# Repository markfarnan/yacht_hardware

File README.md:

# yacht_hardware
Various sensor circuits and boards for Yachts

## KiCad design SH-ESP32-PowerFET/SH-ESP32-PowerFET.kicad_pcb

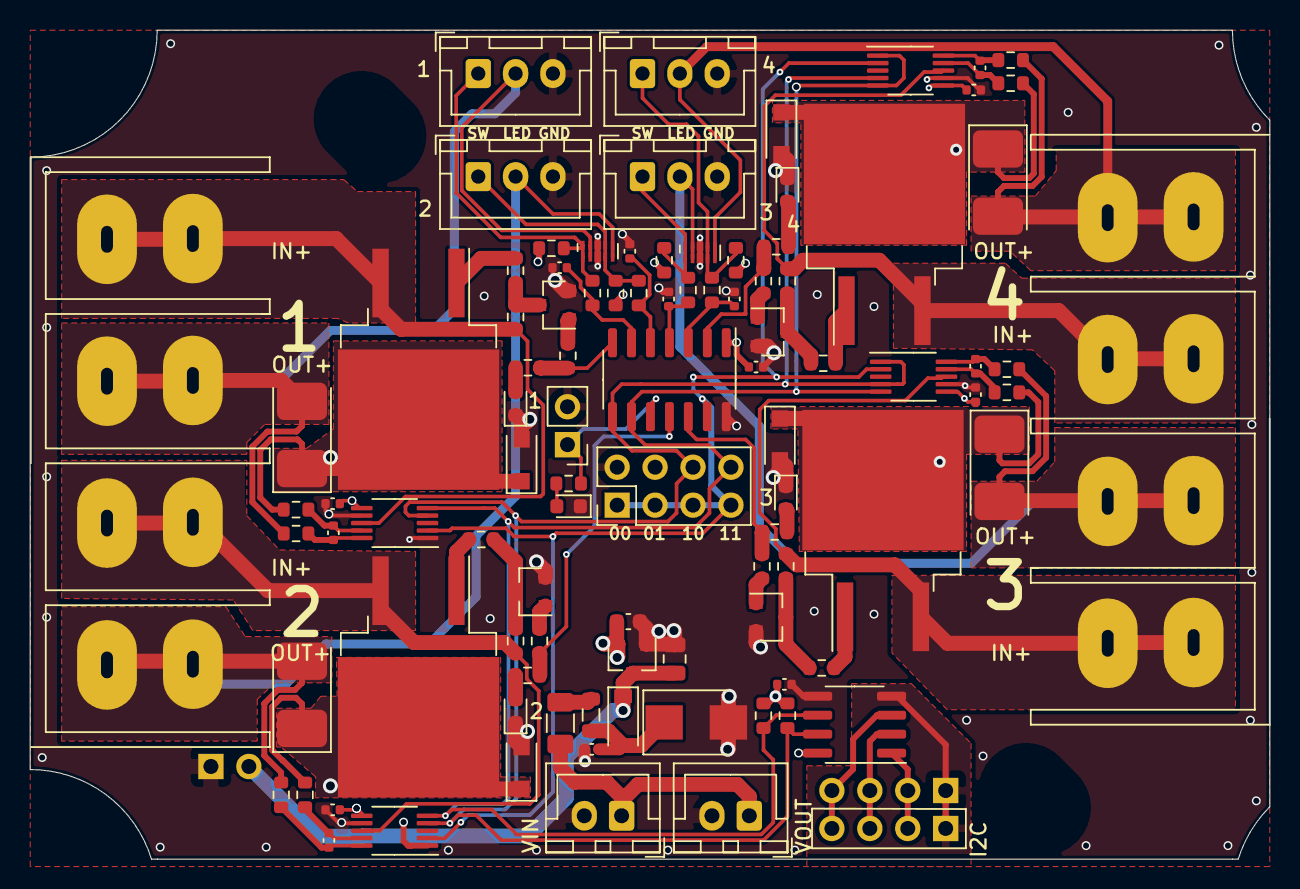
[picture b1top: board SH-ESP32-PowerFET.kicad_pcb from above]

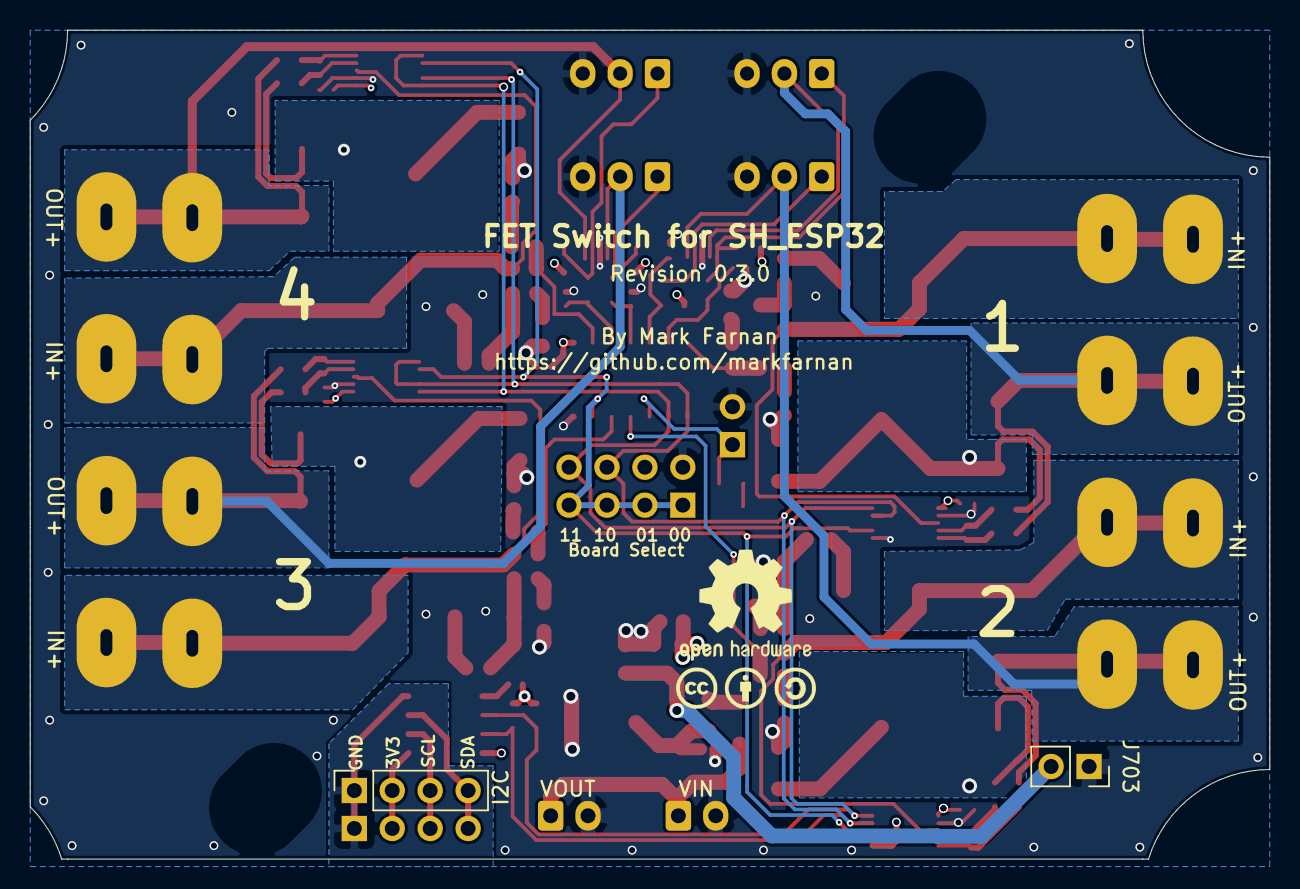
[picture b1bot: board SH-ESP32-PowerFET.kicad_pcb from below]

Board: 4 copper layers, 83.0 x 55.5 mm, 101 parts (2 on the bottom side), 63 nets.

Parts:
C101, C102, C103, C104: 1nf; C_0402_1005Metric
C201, C202, C203, C204, C205, C206, C301, C401, C501, C601: 100nF; C_0402_1005Metric
C701: 2.2uF/50V; C_0805_2012Metric
C702: 10nF/50V; C_0402_1005Metric
C703: 2.2uF/16V; C_0603_1608Metric
D101: RED LED; LED_0603_1608Metric
D301, D401, D501, D601: BLUE LED; LED_0603_1608Metric
D302, D402, D502, D602: SM4007PL; D_SOD-123F
D701: SMBJ33CA; D_SMB
D703: B5819W; D_SOD-123
F701: FSMD012-1206-R; Fuse_1206_3216Metric
FB701: GZ2012D601TF; L_0805_2012Metric
H201, H202: MountingHole; MountingSlot_3.2mm_M3_Unplated
J101: DBT50G-9.5-4P; Connector_9.5mm_ScrewTerminal_4
J102: DBT50G-9.5-2P; Connector_9.5mm_ScrewTerminal_4
J103: AddressSelect; PinHeader_2x04_P2.54mm_Vertical_ReducedCY_Jumper
J105: UPDI; PinHeader_1x02_P2.54mm_Vertical
J106: I2C; PinSocket_1x04_P2.54mm_Vertical
J107, J108, J110, J111: Switch; JST_XH_B3B-XH-A_1x03_P2.50mm_Vertical
J109: I2C; PinHeader_1x04_P2.54mm_Vertical-ShrunkCY
J701: VIN; JST_XH_B2B-XH-A_1x02_P2.50mm_Vertical
J702: VOUT; JST_XH_B2B-XH-A_1x02_P2.50mm_Vertical
J703: VOUT; PinSocket_1x02_P2.54mm_Vertical
Q301, Q401, Q501, Q601: IRLML0030; SOT-23
Q302, Q402, Q502, Q602: IRF5210STRLPBF; TO-263-2
R101, R106, R107, R108, R109, R301, R401, R501, R601: 2k; R_0603_1608Metric
R102, R103, R104, R105, R110, R111, R303, R403, R503, R603: 10k; R_0603_1608Metric
R302, R402, R502, R602: 220R; R_0603_1608Metric
R304, R404, R504, R604: 1k; R_0603_1608Metric
R305, R405, R505, R605: 0.002ohm/3W; D_2512_Shunt
R306, R307, R406, R407, R506, R507, R606, R607: 10R; R_0603_1608Metric
U101: ATtiny1614-SSNR; SOIC-14_3.9x8.7mm_P1.27mm
U102: ISO1540; SOIC-8_3.9x4.9mm_P1.27mm
U103, U701: RCLAMP0524P-N; Diodes_UDFN-10_1.0x2.5mm_P0.5mm
U301, U401, U501, U601: INA226AIDGSR; VSSOP-10_3x3mm_P0.5mm
U702: H7533-H#; SOT-23

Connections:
+3V3: C201.2, C202.2, C203.2, C204.2, C205.2, C206.2, C703.1, J103.4, R102.1, R103.1, R104.1, R105.1, R110.1, R111.1, U101.1, U102.8, U301.6, U401.1, U401.6, U501.6, U601.6, U702.2
/ASEL: J103.1, J103.3, J103.5, J103.7, U101.13, U301.2, U401.2, U501.2, U601.2
/DRVOUT_01: J101.2, J107.2, R305.3, R305.4, R307.2, U701.2, U701.9
/DRVOUT_02: J101.4, J108.2, R405.3, R405.4, R407.2, U701.5, U701.6
/DRVOUT_03: J102.2, J110.2, R505.3, R505.4, R507.2, U103.2, U103.9
/DRVOUT_04: J102.4, J111.2, R605.3, R605.4, R607.2, U103.5, U103.6
/DRVPWR_01: J101.1, Q302.3, R303.1, U301.8
/DRVPWR_02: J101.3, Q402.3, R403.1, U401.8
/DRVPWR_03: J102.1, Q502.3, R503.1, U501.8
/DRVPWR_04: J102.3, Q602.3, R603.1, U601.8
/FET01/VOUT: D302.1, Q302.2, R305.1, R305.2, R306.1
/FET02/VOUT: D402.1, Q402.2, R405.1, R405.2, R406.1
/FET03/VOUT: D502.1, Q502.2, R505.1, R505.2, R506.1
/FET04/VOUT: D602.1, Q602.2, R605.1, R605.2, R606.1
/FETDRIVE_01: R301.1, R302.2, U101.7
/FETDRIVE_02: R401.1, R402.2, U101.11
/FETDRIVE_03: R501.1, R502.2, U101.12
/FETDRIVE_04: R601.1, R602.2, U101.2
/Power-Input/Vin: F701.2, J701.1, J702.1
/Power-Input/Vin_fused: C702.1, D701.1, D703.2, FB701.1
/Power-Input/Vin_protected: C701.1, D703.1, J703.2, U702.3
/SCL: J103.8, R111.2, U101.9, U102.6, U301.5, U401.5, U501.5, U601.1, U601.5
/SCL_CONN: J106.4, J109.4, U102.3
/SDA: J103.6, R110.2, U101.8, U102.7, U301.4, U401.4, U501.1, U501.4, U601.4
/SDA_CONN: J106.3, J109.3, U102.2
/SWIN_1: J107.1, R102.2, R106.2, U701.1, U701.10
/SWIN_2: J108.1, R103.2, R107.2, U701.4, U701.7
/SWIN_3: J110.1, R104.2, R108.2, U103.1, U103.10
/SWIN_4: J111.1, R105.2, R109.2, U103.4, U103.7
/SWITCH_01: C101.1, R106.1, U101.6
/SWITCH_02: C102.1, R107.1, U101.5
/SWITCH_03: C103.1, R108.1, U101.4
/SWITCH_04: C104.1, R109.1, U101.3
/UPDI_LED: J105.1, R101.1, U101.10
/VCC_CONN_3V3: J106.2, J109.2, U102.1
GND: C101.2, C102.2, C103.2, C104.2, C201.1, C202.1, C203.1, C204.1, C205.1, C206.1, C701.2, C702.2, C703.2, D101.1, D301.1, D302.2, D401.1, D402.2, D501.1, D502.2, D601.1, D602.2, D701.2, J103.2, J105.2, J107.3, J108.3, J110.3, J111.3, J701.2, J702.2, J703.1, Q301.2, Q401.2, Q501.2, Q601.2, U101.14, U102.5, U103.3, U103.8, U301.1, U301.7, U401.7, U501.7, U601.7, U701.3, U701.8, U702.1
GNDA: J106.1, J109.1, U102.4
unnamed: C301.1, R306.2, U301.9
unnamed: C301.2, R307.1, U301.10
unnamed: C401.1, R406.2, U401.9
unnamed: C401.2, R407.1, U401.10
unnamed: C501.1, R506.2, U501.9
unnamed: C501.2, R507.1, U501.10
unnamed: C601.1, R606.2, U601.9
unnamed: C601.2, R607.1, U601.10
unnamed: D101.2, R101.2
unnamed: D301.2, R301.2
unnamed: D401.2, R401.2
unnamed: D501.2, R501.2
unnamed: D601.2, R601.2
unnamed: F701.1, FB701.2
unnamed: Q301.1, R302.1
unnamed: Q301.3, R303.2, R304.2
unnamed: Q302.1, R304.1
unnamed: Q401.1, R402.1
unnamed: Q401.3, R403.2, R404.2
unnamed: Q402.1, R404.1
unnamed: Q501.1, R502.1
unnamed: Q501.3, R503.2, R504.2
unnamed: Q502.1, R504.1
unnamed: Q601.1, R602.1
unnamed: Q601.3, R603.2, R604.2
unnamed: Q602.1, R604.1

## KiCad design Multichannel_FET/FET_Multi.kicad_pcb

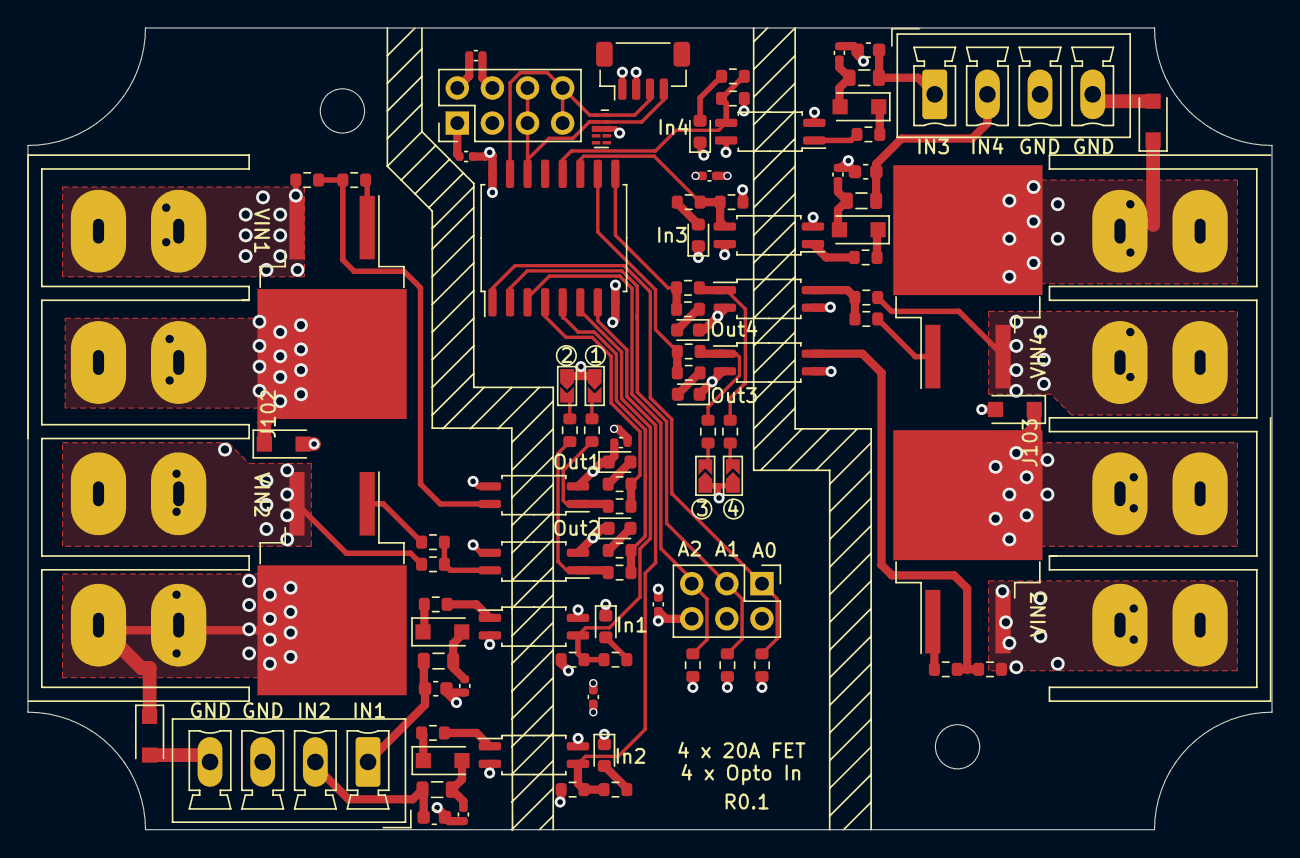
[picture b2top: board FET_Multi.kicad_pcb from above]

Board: 4 copper layers, 90.0 x 58.0 mm, 96 parts (0 on the bottom side), 65 nets.

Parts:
C301, C303, C305, C307: 33pF; C_0402_1005Metric
C302, C304, C306, C308: 33pF/50V; C_0603_1608Metric
C1001, C1002, C1003, C1004, C1005, C1006: 100nF; C_0402_1005Metric
D101, D103, D105, D107, D301, D303, D305, D307: GREEN LED; LED_0603_1608Metric
D102, D104, D106, D108, D302, D304, D306, D308: SM4007PL; D_SOD-123F
FB301, FB302, FB303, FB304: GZ2012D101TF; L_0805_2012Metric
H1001, H1002: MountingHole; MountingHole_3.2mm_M3_Unplated
J101: I2C; PinHeader_2x04_P2.54mm_Vertical
J102, J103: DBT50G-9.5-4P; Connector_9.5mm_ScrewTerminal_4-Reversable
J104: Conn_01x04; JST_SH_BM04B-SRSS-TB_1x04-1MP_P1.00mm_Vertical
J106: ADDR; PinHeader_2x03_P2.54mm_Vertical
J107, J108, J109, J110: PU_ON; SolderJumper-2_P1.3mm_Open_TrianglePad_Narrow
J302, J303: MC 4; PhoenixContact_MCV_1,5_4-G-3.81_1x04_P3.81mm_Vertical
Q101, Q102, Q103, Q104: IRF5210STRLPBF; TO-263-2
R101, R105, R109, R113, R305, R307, R311, R312: 2k; R_0603_1608Metric
R102, R106, R110, R114: 220R; R_0603_1608Metric
R103, R107, R111, R115, R117, R118, R119: 10k; R_0603_1608Metric
R104, R108, R112, R116, R120, R121, R122, R123: 1k; R_0603_1608Metric
R301, R302, R303, R304, R306, R308, R309, R310: 2.2k; R_0603_1608Metric
U101, U102, U103, U104, U301, U302, U303, U304: EL3H7(C)(TA)-G; SOP-4_4.4x2.6mm_P1.27mm
U105: PCF8574T/3,518; SOIC-16W_7.5x10.3mm_P1.27mm
U106: RCLAMP0524P-N; Diodes_UDFN-10_1.0x2.5mm_P0.5mm

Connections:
+3V3: C1001.2, C1002.2, C1003.2, C1004.2, C1005.2, C1006.2, J101.3, J101.4, J104.2, J106.2, J106.4, J106.6, J107.1, J108.1, J109.1, J110.1, U105.16, U301.4, U302.4, U303.4, U304.4
/A0: J106.1, R119.1, U105.1
/A1: J106.3, R118.1, U105.2
/A2: J106.5, R117.1, U105.3
/GPIO0: R101.1, R102.2, U105.4
/GPIO1: R105.1, R106.2, U105.5
/GPIO4: R113.1, R114.2, U105.9
/GPIO5: R109.1, R110.2, U105.10
/Opto Input/ISO_IN_1: C302.1, FB301.1, J302.1
/Opto Input/ISO_IN_2: C304.1, FB302.1, J302.2
/Opto Input/ISO_IN_3: C306.1, FB303.1, J303.1
/Opto Input/ISO_IN_4: C308.1, FB304.1, J303.2
/SCL: J101.5, J101.6, J104.4, U105.14, U106.2, U106.9
/SDA: J101.7, J101.8, J104.3, U105.15, U106.1, U106.10
/VIN1: J102.1, Q101.3, R103.1
/VIN2: J102.3, Q102.3, R107.1
/VIN3: J103.1, Q103.3, R111.1
/VIN4: J103.3, Q104.3, R115.1
/VOUT1: D102.1, J102.2, Q101.2
/VOUT2: D104.1, J102.4, Q102.2
/VOUT3: D106.1, J103.2, Q103.2
/VOUT4: D108.1, J103.4, Q104.2
GND: C1001.1, C1002.1, C1003.1, C1004.1, C1005.1, C1006.1, D101.1, D103.1, D105.1, D107.1, D301.1, D303.1, D305.1, D307.1, J101.1, J101.2, J104.1, R117.2, R118.2, R119.2, R301.1, R303.1, R309.1, R310.1, U101.2, U102.2, U103.2, U104.2, U105.8, U106.3, U106.8
GND1: C301.2, C302.2, C303.2, C304.2, D102.2, D104.2, J302.3, J302.4, U101.3, U102.3, U301.2, U302.2
GND2: C305.2, C306.2, C307.2, C308.2, D106.2, D108.2, J303.3, J303.4, U103.3, U104.3, U303.2, U304.2
GPIO2: R301.2, R305.1, U105.6, U301.3
GPIO3: R303.2, R307.1, U105.7, U302.3
GPIO6: R309.2, R311.1, U105.11, U303.3
GPIO7: R310.2, R312.1, U105.12, U304.3
unnamed: C301.1, D302.2, FB301.2
unnamed: C303.1, D304.2, FB302.2
unnamed: C305.1, D306.2, FB303.2
unnamed: C307.1, D308.2, FB304.2
unnamed: D101.2, R101.2
unnamed: D103.2, R105.2
unnamed: D105.2, R109.2
unnamed: D107.2, R113.2
unnamed: D301.2, R305.2
unnamed: D302.1, R302.1
unnamed: D303.2, R307.2
unnamed: D304.1, R304.1
unnamed: D305.2, R311.2
unnamed: D306.1, R306.1
unnamed: D307.2, R312.2
unnamed: D308.1, R308.1
unnamed: J107.2, R120.1
unnamed: J108.2, R121.1
unnamed: J109.2, R122.1
unnamed: J110.2, R123.1
unnamed: Q101.1, R104.1
unnamed: Q102.1, R108.1
unnamed: Q103.1, R112.1
unnamed: Q104.1, R116.1
unnamed: R102.1, R120.2, U101.1
unnamed: R103.2, R104.2, U101.4
unnamed: R106.1, R121.2, U102.1
unnamed: R107.2, R108.2, U102.4
unnamed: R110.1, R123.2, U103.1
unnamed: R111.2, R112.2, U103.4
unnamed: R114.1, R122.2, U104.1
unnamed: R115.2, R116.2, U104.4
unnamed: R302.2, U301.1
unnamed: R304.2, U302.1
unnamed: R306.2, U304.1
unnamed: R308.2, U303.1

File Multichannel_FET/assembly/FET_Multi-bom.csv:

Comment,Designator,Footprint,LCSC
"100nF","C1001,C1002,C1003,C1004,C1005,C1006","Capacitor_SMD:C_0402_1005Metric","C1525"
"33pF","C301,C303,C305,C307","Capacitor_SMD:C_0402_1005Metric","C1562"
"33pF/50V","C302,C304,C306,C308","Capacitor_SMD:C_0603_1608Metric","C1663"
"GREEN LED","D101,D103,D105,D107,D301,D303,D305,D307","LED_SMD:LED_0603_1608Metric","C72043"
"SM4007PL","D102,D104,D106,D108,D302,D304,D306,D308","Diode_SMD:D_SOD-123F","C64898"
"GZ2012D101TF","FB301,FB302,FB303,FB304","Inductor_SMD:L_0805_2012Metric","C1015"
"MountingHole","H1001,H1002","SH-ESP32:MountingHole_3.2mm_M3_Unplated",""
"I2C","J101","Connector_PinHeader_2.54mm:PinHeader_2x04_P2.54mm_Vertical",""
"DBT50G-9.5-4P","J102,J103","FET_Multi:Connector_9.5mm_ScrewTerminal_4-Reversable","C395960"
"Conn_01x04","J104","Connector_JST:JST_SH_BM04B-SRSS-TB_1x04-1MP_P1.00mm_Vertical","C145961"
"ADDR","J106","Connector_PinHeader_2.54mm:PinHeader_2x03_P2.54mm_Vertical",""
"PU_ON","J107,J108,J109,J110","FET_Multi:SolderJumper-2_P1.3mm_Open_TrianglePad_Narrow",""
"MC 4","J302,J303","Connector_Phoenix_MC:PhoenixContact_MCV_1,5_4-G-3.81_1x04_P3.81mm_Vertical","C458128"
"IRF5210STRLPBF","Q101,Q102,Q103,Q104","Package_TO_SOT_SMD:TO-263-2","C2622"
"2k","R101,R105,R109,R113,R305,R307,R311,R312","Resistor_SMD:R_0603_1608Metric","C22975"
"220R","R102,R106,R110,R114","Resistor_SMD:R_0603_1608Metric","C22962"
"10k","R103,R107,R111,R115,R117,R118,R119","Resistor_SMD:R_0603_1608Metric","C25804"
"1k","R104,R108,R112,R116,R120,R121,R122,R123","Resistor_SMD:R_0603_1608Metric","C21190"
"2.2k","R301,R302,R303,R304,R306,R308,R309,R310","Resistor_SMD:R_0603_1608Metric","C4190"
"EL3H7(C)(TA)-G","U101,U102,U103,U104,U301,U302,U303,U304","Package_SO:SOP-4_4.4x2.6mm_P1.27mm","C92243"
"PCF8574T/3,518","U105","Package_SO:SOIC-16W_7.5x10.3mm_P1.27mm","C7605"
"RCLAMP0524P-N","U106","Package_DFN_QFN:Diodes_UDFN-10_1.0x2.5mm_P0.5mm","C316044"

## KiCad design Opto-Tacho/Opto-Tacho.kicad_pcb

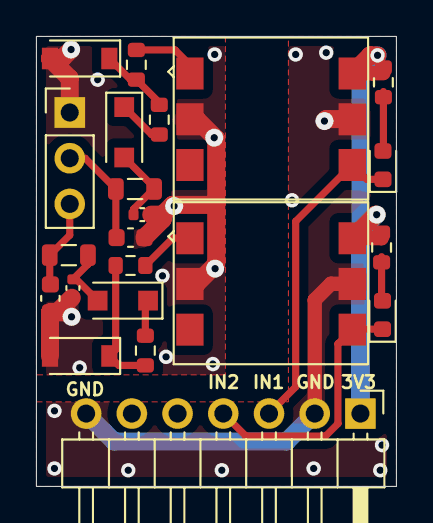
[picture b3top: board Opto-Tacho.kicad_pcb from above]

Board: 2 copper layers, 20.0 x 25.0 mm, 22 parts (0 on the bottom side), 17 nets.

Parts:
C101, C103: 33pF; C_0402_1005Metric
C102, C104: 33pF/50V; C_0603_1608Metric
D101, D104: GREEN LED; LED_0603_1608Metric
D102, D105: MM1Z4V7B; D_SOD-123
D103, D106: SM4007PL; D_SOD-123F
FB101, FB102: GZ2012D101TF; L_0805_2012Metric
J101: Interface; PinHeader_1x07_P2.54mm_Horizontal
J901: Conn_01x03; PinHeader_1x03_P2.54mm_Vertical
R101, R103, R104, R106: 1k; R_0603_1608Metric
R102, R105: 330; R_0603_1608Metric
U101, U102: H11L1SR2M; SMT-6_6.4x8.5x2.54P

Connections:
+3V3: J101.1, R101.1, R104.1, U101.6, U102.6
/GPIO_1: D101.1, J101.3, U101.4
/GPIO_2: D104.1, J101.4, U102.4
/ISO_GND: C101.2, C102.2, C103.2, C104.2, D102.2, D105.2, J901.1, U101.2, U102.2
/ISO_IN_1: C102.1, FB101.1, J901.2
/ISO_IN_2: C104.1, FB102.1, J901.3
GND: J101.2, J101.7, U101.5, U102.5
unnamed: C101.1, D103.2, FB101.2
unnamed: C103.1, D106.2, FB102.2
unnamed: D101.2, R101.2
unnamed: D102.1, R102.1, R103.2
unnamed: D103.1, R103.1
unnamed: D104.2, R104.2
unnamed: D105.1, R105.1, R106.2
unnamed: D106.1, R106.1
unnamed: R102.2, U101.1
unnamed: R105.2, U102.1

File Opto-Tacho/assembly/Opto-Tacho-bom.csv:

Comment,Designator,Footprint,LCSC
"33pF","C101,C103","Capacitor_SMD:C_0402_1005Metric","C1562"
"33pF/50V","C102,C104","Capacitor_SMD:C_0603_1608Metric","C1663"
"GREEN LED","D101,D104","LED_SMD:LED_0603_1608Metric","C72043"
"MM1Z4V7B","D102,D105","Diode_SMD:D_SOD-123","C438304"
"SM4007PL","D103,D106","Diode_SMD:D_SOD-123F","C64898"
"GZ2012D101TF","FB101,FB102","Inductor_SMD:L_0805_2012Metric","C1015"
"Interface","J101","Connector_PinHeader_2.54mm:PinHeader_1x07_P2.54mm_Horizontal",""
"Conn_01x03","J901","Connector_PinHeader_2.54mm:PinHeader_1x03_P2.54mm_Vertical","C358686"
"330","R102,R105","Resistor_SMD:R_0603_1608Metric","C23138"
"1k","R101,R103,R104,R106","Resistor_SMD:R_0603_1608Metric","C21190"
"H11L1SR2M","U101,U102","yacht_hardware:SMT-6_6.4x8.5x2.54P","C20082"

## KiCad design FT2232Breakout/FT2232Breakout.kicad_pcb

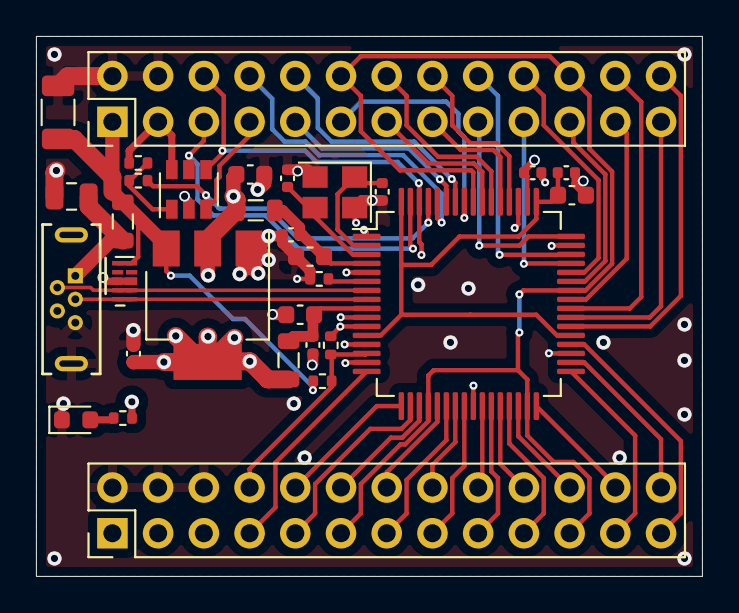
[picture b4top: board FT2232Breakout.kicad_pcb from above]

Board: 4 copper layers, 37.0 x 30.0 mm, 31 parts (0 on the bottom side), 53 nets.

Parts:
C101, C103, C109: 4.7uF/16V; C_0603_1608Metric
C102: 4.7uF; C_0603_1608Metric
C104, C107: 30pf; C_0402_1005Metric
C105, C106, C108, C110, C305: 100nF; C_0402_1005Metric
C301: 10uF/50V; C_1206_3216Metric
C503: 1uF/50V; C_0805_2012Metric
D101: RED LED; LED_0603_1608Metric
FB101, FB102, FB401: GZ2012D601TF; L_0805_2012Metric
J101: USB_B_Micro; USB_Micro-B_Wuerth_614105150721_Vertical
J102: IO2; PinHeader_2x13_P2.54mm_Vertical
J103: IO1; PinHeader_2x13_P2.54mm_Vertical
R101, R104: 10k; R_0402_1005Metric
R102: 12k; R_0402_1005Metric
R103, R106: 2k; R_0402_1005Metric
R105: 15k; R_0402_1005Metric
U101: AMS1117-3.3; SOT-223-3_TabPin2
U102: 93LC56BT-I/OT; SOT-23-6
U103: FT2232HL; LQFP-64_10x10mm_P0.5mm
U402: RCLAMP0524P-N; Diodes_UDFN-10_1.0x2.5mm_P0.5mm
Y101: X322512MSB4SI; Crystal_SMD_3225-4Pin_3.2x2.5mm

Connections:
+3V3: C101.1, C108.1, C305.1, FB101.2, FB102.2, J102.3, J103.1, J103.3, J103.5, R101.1, R106.1, U101.2, U102.6, U103.50
+5V: C301.1, FB401.1, J102.1, R105.1, U101.3, U402.5, U402.6
/AC0: J103.18, U103.26
/AC1: J103.17, U103.27
/AC2: J103.20, U103.28
/AC3: J103.19, U103.29
/AC4: J103.22, U103.30
/AC5: J103.24, U103.32
/AC6: J103.23, U103.33
/AC7: J103.26, U103.34
/AD0: J103.7, U103.16
/AD1: J103.10, U103.17
/AD2: J103.9, U103.18
/AD3: J103.12, U103.19
/AD4: J103.14, U103.21
/AD5: J103.13, U103.22
/AD6: J103.16, U103.23
/AD7: J103.15, U103.24
/BC0: J102.17, U103.48
/BC1: J102.16, U103.52
/BC2: J102.15, U103.53
/BC3: J102.14, U103.54
/BC4: J102.13, U103.55
/BC5: J102.11, U103.57
/BC6: J102.10, U103.58
/BC7: J102.9, U103.59
/BD0: J102.26, U103.38
/BD1: J102.25, U103.39
/BD2: J102.24, U103.40
/BD3: J102.23, U103.41
/BD4: J102.21, U103.43
/BD5: J102.20, U103.44
/BD6: J102.19, U103.45
/BD7: J102.18, U103.46
/CLK: J102.6, U102.4, U103.62
/CS: J102.5, U102.5, U103.63
/DATA: J102.7, R103.1, U102.3, U103.61
/PWREN#: J102.8, U103.60
/RESET#: J103.8, R104.1, R105.2, U103.14
/SUSPEND#: J103.25, U103.36
/USB_D+: J101.3, U103.8, U402.1, U402.10
/USB_D-: J101.2, U103.7, U402.2, U402.9
/VBUS: C503.1, FB401.2, J101.1
/VCORE: C102.1, C105.1, U103.12, U103.37, U103.49, U103.64
/VIO: J102.12, J102.22, J103.11, J103.21, U103.20, U103.31, U103.42, U103.56
/VPHY: C103.1, C106.1, FB102.1, U103.4
/VPLL: C109.1, C110.1, FB101.1, U103.9
GND: C101.2, C102.2, C103.2, C104.1, C105.2, C106.2, C107.1, C108.2, C109.2, C110.2, C301.2, C305.2, C503.2, D101.1, J101.5, J101.6, J102.2, J102.4, J103.2, J103.4, J103.6, R102.2, R104.2, U101.1, U102.2, U103.1, U103.5, U103.10, U103.11, U103.13, U103.15, U103.25, U103.35, U103.47, U103.51, U402.3, U402.8, Y101.2, Y101.4
unnamed: C104.2, U103.2, Y101.1
unnamed: C107.2, U103.3, Y101.3
unnamed: D101.2, R106.2
unnamed: R101.2, R103.2, U102.1
unnamed: R102.1, U103.6

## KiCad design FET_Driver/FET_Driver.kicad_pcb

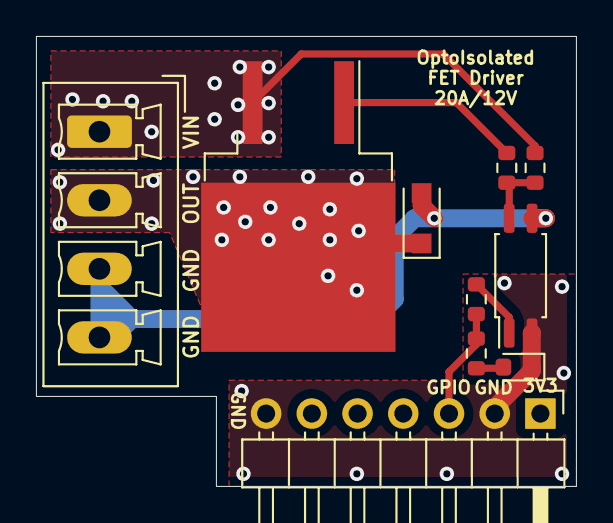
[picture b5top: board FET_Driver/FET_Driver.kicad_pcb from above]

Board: 2 copper layers, 30.0 x 25.0 mm, 10 parts (0 on the bottom side), 9 nets.

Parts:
D101: SM4007PL; D_SOD-123F
D102: GREEN LED; LED_0603_1608Metric
J101: Interface; PinHeader_1x07_P2.54mm_Horizontal
J102: Out; PhoenixContact_MCV_1,5_4-G-3.81_1x04_P3.81mm_Vertical
Q101: IRF5210STRLPBF; TO-263-2
R101: 10k; R_0603_1608Metric
R102, R103: 1k; R_0603_1608Metric
R901: 220R; R_0603_1608Metric
U101: EL3H7(C)(TA)-G; SOP-4_4.4x2.6mm_P1.27mm

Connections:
/GPIO: J101.3, R103.1, R901.2
/ISO_GND: D101.2, J102.3, J102.4, U101.3
/ISO_OUT: D101.1, J102.2, Q101.2
/ISO_VIN: J102.1, Q101.3, R101.1
GND: D102.1, J101.2, J101.7, U101.2
unnamed: D102.2, R103.2
unnamed: Q101.1, R102.1
unnamed: R101.2, R102.2, U101.4
unnamed: R901.1, U101.1

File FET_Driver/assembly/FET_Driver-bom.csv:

Comment,Designator,Footprint,LCSC
"SM4007PL","D101","Diode_SMD:D_SOD-123F","C64898"
"GREEN LED","D102","LED_SMD:LED_0603_1608Metric","C72043"
"Interface","J101","Connector_PinHeader_2.54mm:PinHeader_1x07_P2.54mm_Horizontal",""
"Out","J102","Connector_Phoenix_MC:PhoenixContact_MCV_1,5_4-G-3.81_1x04_P3.81mm_Vertical",""
"IRF5210STRLPBF","Q101","Package_TO_SOT_SMD:TO-263-2","C2622"
"10k","R101","Resistor_SMD:R_0603_1608Metric","C25804"
"1k","R102,R103","Resistor_SMD:R_0603_1608Metric","C21190"
"220R","R901","Resistor_SMD:R_0603_1608Metric","C22962"
"EL3H7(C)(TA)-G","U101","Package_SO:SOP-4_4.4x2.6mm_P1.27mm","C92243"

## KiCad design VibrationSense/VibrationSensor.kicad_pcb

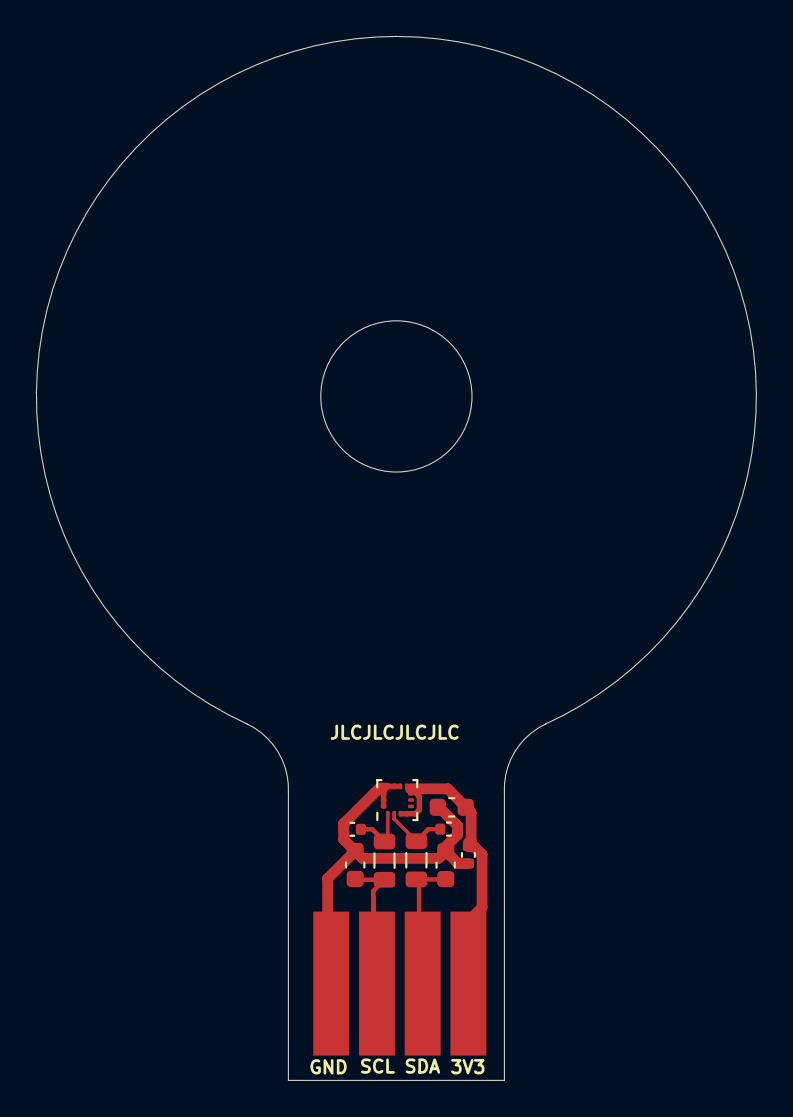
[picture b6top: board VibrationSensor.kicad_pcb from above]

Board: 2 copper layers, 40.0 x 58.0 mm, 11 parts (0 on the bottom side), 6 nets.

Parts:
C101: 4.7uF; C_0603_1608Metric
C102, C103: 33pF/50V; C_0603_1608Metric
C104, C105: 33pF; C_0402_1005Metric
C305: 100nF; C_0402_1005Metric
FB101, FB102: GZ2012D101TF; L_0805_2012Metric
H101: MountingHole; MountingHole_8.4mm_M8
J101: Interface; Header_1x04_P2.54mm_SurfaceWires
U101: LIS2DH12TR; LGA-14_2x2mm_P0.35mm_LayoutBorder3x4y

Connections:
+3V3: C101.2, C305.2, J101.1, U101.3, U101.4, U101.7, U101.8
/SCL: C103.1, FB102.1, J101.3
/SDA: C102.1, FB101.1, J101.2
GND: C101.1, C102.2, C103.2, C104.2, C105.2, C305.1, J101.4, U101.9, U101.10, U101.11, U101.12, U101.13, U101.14
unnamed: C104.1, FB101.2, U101.2
unnamed: C105.1, FB102.2, U101.1

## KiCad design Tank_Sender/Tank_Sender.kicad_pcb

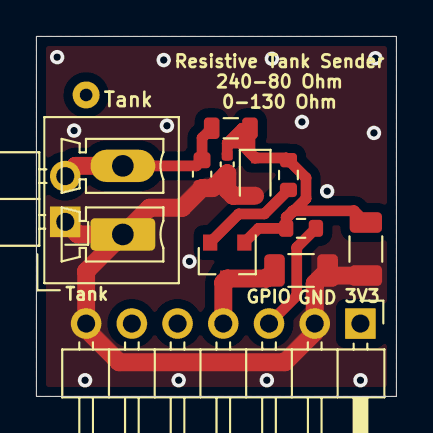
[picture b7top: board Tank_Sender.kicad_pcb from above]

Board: 2 copper layers, 20.0 x 20.0 mm, 12 parts (0 on the bottom side), 6 nets.

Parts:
C101, C102: 10uF/50V; C_1206_3216Metric
C103: 33pF; C_0402_1005Metric
C104: 33pF/50V; C_0603_1608Metric
D101: KDZ3.3V-RTK/P; D_SOD-323
FB101: GZ2012D101TF; L_0805_2012Metric
J101: Interface; PinHeader_1x07_P2.54mm_Horizontal
J102: TANK; PinHeader_1x02_P2.54mm_Horizontal
J103: TANK; PhoenixContact_MCV_1,5_2-G-3.81_1x02_P3.81mm_Vertical
R101: 2K; R_0603_1608Metric
R102: 470; R_0603_1608Metric
U101: H7550-H#; SOT-23

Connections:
/GPIO_AD: J101.3, R101.1
/Tank: C104.1, FB101.1, J102.2, J103.2
/VIN_PROT: C101.1, J101.4, U101.3
GND: C101.2, C102.2, C103.2, C104.2, D101.2, J101.2, J101.7, J102.1, J103.1
unnamed: C102.1, C103.1, D101.1, FB101.2, R101.2, R102.2, U101.1
unnamed: R102.1, U101.2

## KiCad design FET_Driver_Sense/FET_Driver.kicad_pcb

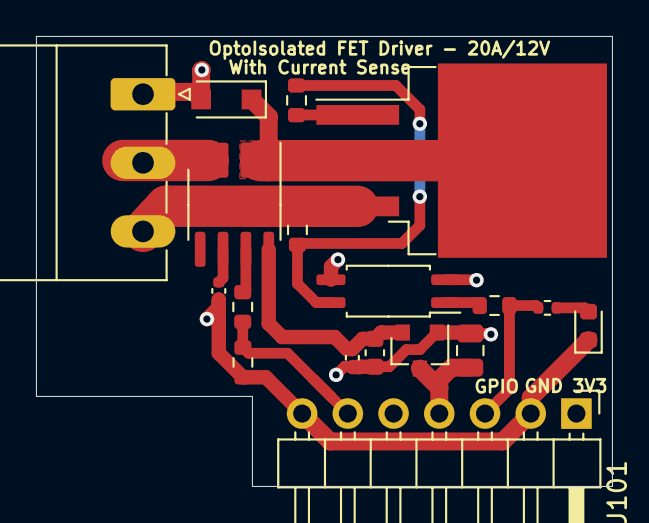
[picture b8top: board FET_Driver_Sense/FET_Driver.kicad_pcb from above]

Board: 2 copper layers, 32.0 x 25.0 mm, 18 parts (0 on the bottom side), 15 nets.

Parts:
C101, C102: 100nF; C_0402_1005Metric
C603: 2.2uF/50V; C_0805_2012Metric
C605: 2.2uF/16V; C_0603_1608Metric
D101: SM4007PL; D_SOD-123F
D102: GREEN LED; LED_0603_1608Metric
J101: Interface; PinHeader_1x07_P2.54mm_Horizontal
J102: Out; PhoenixContact_MC_1,5_3-G-3.81_1x03_P3.81mm_Horizontal
Q101: IRF5210STRLPBF; TO-263-2
R101, R103: 10k; R_0603_1608Metric
R102: 1k; R_0603_1608Metric
R104: 2k; R_0603_1608Metric
R105: 2k; R_0402_1005Metric
R901: 220R; R_0603_1608Metric
U101: EL3H7(C)(TA)-G; SOP-4_4.4x2.6mm_P1.27mm
U102: ACS712ELCTR-20A-T; SOIC-8_3.9x4.9mm_P1.27mm
U603: H7550-H#; SOT-23

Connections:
+5V: C101.2, C605.1, U102.8, U603.2
/GPIO: J101.3, R105.1, R901.2
/ISO_GND: D101.2, J102.1, U101.3
/ISO_OUT: J102.2, U102.3, U102.4
/ISO_OUT_RAW: D101.1, Q101.2, U102.1, U102.2
/ISO_VIN: J102.3, Q101.3, R101.1
/Sense: J101.6, R103.1, R104.2
/VIN: C603.1, J101.4, U603.3
GND: C101.1, C102.2, C603.2, C605.2, D102.1, J101.2, J101.7, R103.2, U101.2, U603.1
unnamed: C102.1, U102.6
unnamed: D102.2, R105.2
unnamed: Q101.1, R102.1
unnamed: R101.2, R102.2, U101.4
unnamed: R104.1, U102.7
unnamed: R901.1, U101.1

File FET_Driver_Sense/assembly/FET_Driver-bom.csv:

Comment,Designator,Footprint,LCSC
"100nF","C101,C102","Capacitor_SMD:C_0402_1005Metric","C1525"
"2.2uF/50V","C603","Capacitor_SMD:C_0805_2012Metric","C50254"
"2.2uF/16V","C605","Capacitor_SMD:C_0603_1608Metric","C23630"
"SM4007PL","D101","Diode_SMD:D_SOD-123F","C64898"
"GREEN LED","D102","LED_SMD:LED_0603_1608Metric","C72043"
"Interface","J101","Connector_PinHeader_2.54mm:PinHeader_1x07_P2.54mm_Horizontal",""
"Out","J102","Connector_Phoenix_MC:PhoenixContact_MC_1,5_3-G-3.81_1x03_P3.81mm_Horizontal",""
"IRF5210STRLPBF","Q101","Package_TO_SOT_SMD:TO-263-2","C2622"
"10k","R101,R103","Resistor_SMD:R_0603_1608Metric","C25804"
"1k","R102","Resistor_SMD:R_0603_1608Metric","C21190"
"2k","R104","Resistor_SMD:R_0603_1608Metric","C22975"
"2k","R105","Resistor_SMD:R_0402_1005Metric","C12447"
"220R","R901","Resistor_SMD:R_0603_1608Metric","C22962"
"EL3H7(C)(TA)-G","U101","Package_SO:SOP-4_4.4x2.6mm_P1.27mm","C92243"
"ACS712ELCTR-20A-T","U102","Package_SO:SOIC-8_3.9x4.9mm_P1.27mm","C10681"
"H7550-H#","U603","Package_TO_SOT_SMD:SOT-23","C277875"

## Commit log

2020-11-20 Initial version with AC Current Transformer, MiniHatProt and Tanksender sensor adapters
2020-11-20 Standardize on 20mm x 20mm boards with 7pin header
2020-11-21 New GND Pin. Added PI Filters to all inputs. Refined Layout
2020-11-21 FET Driver with Current Sense
2020-11-22 Opto Tacho (Schmidtt), Fixes to FET_Driver_Sense
2020-11-24 Fix Libraries
2020-11-24 Fix Symbol Libraries
2020-11-27 Production Tidyup - LCSC Part Numbers
2020-11-27 FET Driver - LCSC Parts tidy up
2020-11-27 Opto - LCSC Parts added
2020-11-27 Vibration Sensor - Initial Version 0.1
2020-11-27 Add LCSC part to Accelerometer
2020-11-27 Assembly files for R 0.1
2020-11-28 Change to LIS2DH12 (from HH). DH has higher sampling rate, and is cheaper.
2020-11-28 Update Fabrication files for Chip change
2020-11-28 Fix Resistor sizes to all are 603
2020-11-28 Re-arrange FET Driver PCB for better High current tracks
2020-11-28 Change FET VIN/OUT connector to 4 Pin to reduce stock parts
2020-11-28 Initial Version - FT2232HL Breakout board
2020-11-28 FT2232HL Breakout - R0.1 Assembly files
2020-11-28 Add file fixer script for FET Driver
2020-11-28 FET_Driver Production files
2020-11-29 Fix Footprint center for Opto
2020-11-29 Production files for Opto-Tacho
2020-11-29 Add file fixer script for FET Driver
    (cherry picked from commit 5fe6a2fc87ed3db5ff3dbfc584127ee4adedae34)
2020-11-29 FT2232 Proto board
2020-11-29 Opto-Tach - Change Opto's to SMD part
2020-11-29 FT2232 - Proto - Production files
2020-11-30 Initial Commit - Multichannel FET
2020-11-30 Silkscreen Updates - MultiChannel_FET
2020-11-30 100x68x50 Box board Blank
2020-11-30 Fix JLCPCB-Fix file for MultiFET
2020-11-30 Production files for FET_Multi R0.1
2020-12-03 SH-ESP32 / I2C 4Ch PowerFET board - Initial
2020-12-03 Updated Shunt Part number
2020-12-03 Production files for SH-ESP32-PowerFET
2020-12-24 Major Refactor - Based on new requirments from Karl and feedback. - Made from latest blank with more PCB area, and new interconnect positions for I2C, GPIO etc - Removed opto couplers - I2C now isola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
2020-12-24 Fix I2C Address selection to support up to 4 boards - Add pullups to I2C
2020-12-25 Tidy Planes on back side - Change I2C header to Socket for HAT connection to SH_ESP32
2020-12-25 Change Buck PSU for a LDO Regulator - Allowed input from VIN-Protected from SH-ESP32 when in HAT mode. (2 pin socket). - Saves wiring and sockets etc. - Shoved ScrewTerminal to permit VIN-Prot header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

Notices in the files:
Multichannel_FET/FET_Multi.kicad_pcb:
Sailor Hat for ESP32 is licensed under CC BY-SA 4.0.
